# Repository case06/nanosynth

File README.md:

# nanosynth

[![In cooperation with Open Source Ecology Germany](
    https://custom-icon-badges.demolab.com/badge/-OSEG-555555.svg?logo=oseg_logo)](
    https://opensourceecology.de)

Simple synth with MIDI interface, based on Arduino Nano

The KiCAD-sourcefiles of the current version can be viewed or modified with KiCAD version 5.0.2 or higher.

<p></p>

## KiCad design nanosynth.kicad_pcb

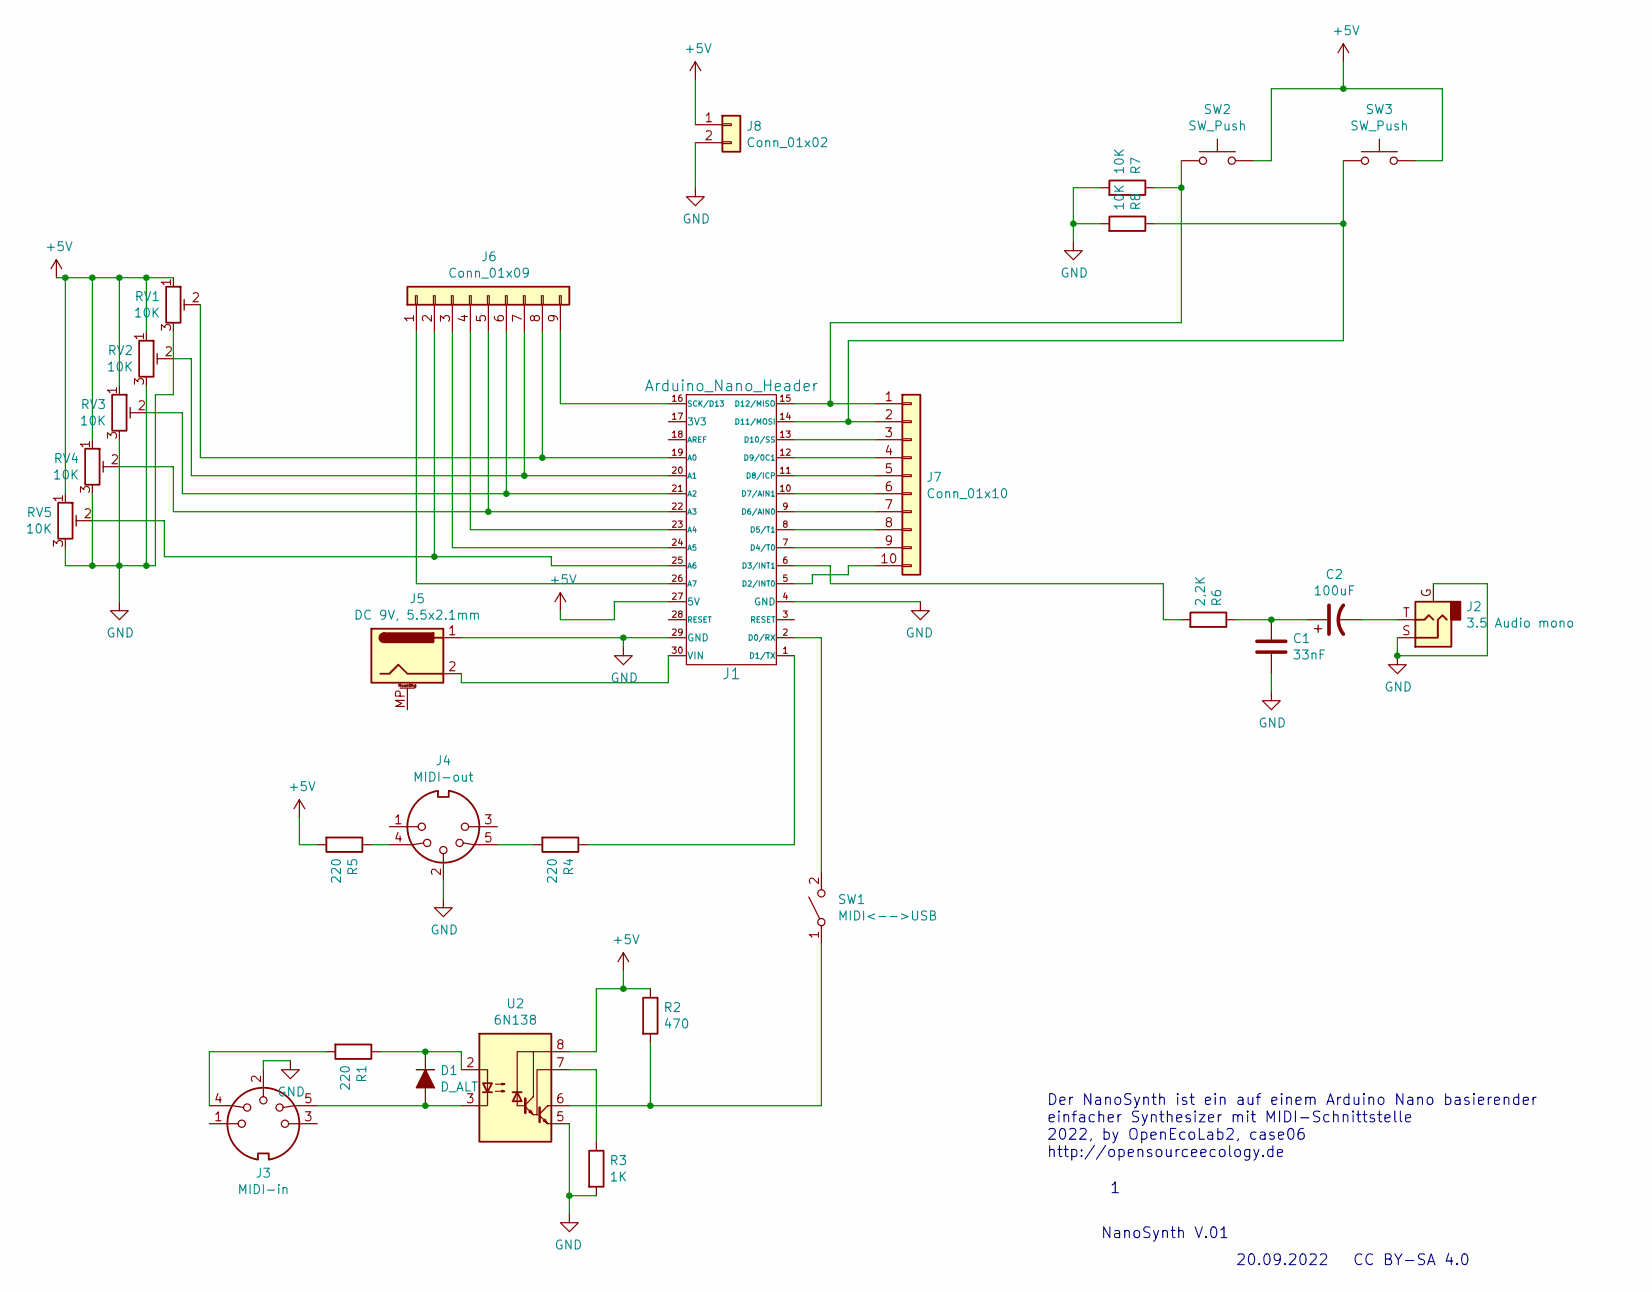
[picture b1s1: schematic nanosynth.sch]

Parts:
C1: 33nF; C_Rect_L7.5mm_W6.5mm_P5.00mm
C2: 100uF; CP_Radial_D8.0mm_P5.00mm
D1: D_ALT; D_DO-35_SOD27_P7.62mm_Horizontal
J1: Arduino_Nano_Header; arduino_nano_header
J2: 3.5 Audio mono; Jack_3.5mm_CUI_SJ1-3533NG_Horizontal
J3: MIDI-in; PinHeader_1x05_P2.54mm_Vertical
J4: MIDI-out; PinHeader_1x05_P2.54mm_Vertical
J5: DC 9V, 5.5x2.1mm; BarrelJack_Horizontal
J6: Conn_01x09; PinHeader_1x09_P2.54mm_Vertical
J7: Conn_01x10; PinHeader_1x10_P2.54mm_Vertical
J8: Conn_01x02; PinHeader_1x02_P2.54mm_Vertical
R1, R4, R5: 220; R_Axial_DIN0309_L9.0mm_D3.2mm_P5.08mm_Vertical
R2: 470; R_Axial_DIN0309_L9.0mm_D3.2mm_P5.08mm_Vertical
R3: 1K; R_Axial_DIN0309_L9.0mm_D3.2mm_P5.08mm_Vertical
R6: 2,2K; R_Axial_DIN0309_L9.0mm_D3.2mm_P5.08mm_Vertical
R7, R8: 10K; R_Axial_DIN0309_L9.0mm_D3.2mm_P5.08mm_Vertical
RV1, RV2, RV3, RV4, RV5: 10K; Potentiometer_Vishay_T73XW_Horizontal
SW1: MIDI<-->USB; PinHeader_1x02_P2.54mm_Vertical
SW2, SW3: SW_Push; PinHeader_1x02_P2.54mm_Vertical
U2: 6N138; DIP-8_W7.62mm_LongPads

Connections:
+5V: J1.27 (5V), J8.1, R2.1, R5.2, RV1.1, RV2.1, RV3.1, RV4.1, RV5.1, SW2.2, SW3.2, U2.8 (VCC)
GND: C1.2, J1.4 (GND), J1.29 (GND), J2.G, J2.S, J3.2, J4.2, J5.1, J8.2, R3.2, R7.2, R8.2, RV1.3, RV2.3, RV3.3, RV4.3, RV5.3, U2.5 (GND)
unnamed: C1.1, C2.1, R6.1
unnamed: C2.2, J2.T
unnamed: D1.1 (K), R1.1, U2.2 (C1)
unnamed: D1.2 (A), J3.5, U2.3 (C2)
unnamed: J1.1 (D1/TX), R4.1
unnamed: J1.2 (D0/RX), SW1.2 (B)
unnamed: J1.5 (D2/INT0), J7.10
unnamed: J1.6 (D3/INT1), R6.2
unnamed: J1.7 (D4/T0), J7.9
unnamed: J1.8 (D5/T1), J7.8
unnamed: J1.9 (D6/AIN0), J7.7
unnamed: J1.10 (D7/AIN1), J7.6
unnamed: J1.11 (D8/ICP), J7.5
unnamed: J1.12 (D9/0C1), J7.4
unnamed: J1.13 (D10/SS), J7.3
unnamed: J1.14 (D11/MOSI), J7.2, R8.1, SW3.1
unnamed: J1.15 (D12/MISO), J7.1, R7.1, SW2.1
unnamed: J1.16 (SCK/D13), J6.9
unnamed: J1.19 (A0), J6.8, RV1.2
unnamed: J1.20 (A1), J6.7, RV2.2
unnamed: J1.21 (A2), J6.6, RV3.2
unnamed: J1.22 (A3), J6.5, RV4.2
unnamed: J1.23 (A4), J6.4
unnamed: J1.24 (A5), J6.3
unnamed: J1.25 (A6), J6.2, RV5.2
unnamed: J1.26 (A7), J6.1
unnamed: J1.30 (VIN), J5.2
unnamed: J3.4, R1.2
unnamed: J4.4, R5.1
unnamed: J4.5, R4.2
unnamed: R2.2, SW1.1 (A), U2.6 (VO2)
unnamed: R3.1, U2.7 (VO1)

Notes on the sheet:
NanoSynth V.01
20.09.2022
Der NanoSynth ist ein auf einem Arduino Nano basierender einfacher Synthesizer mit MIDI-Schnittstelle 2022, by OpenEcoLab2, case06 http://opensourceecology.de
CC BY-SA 4.0

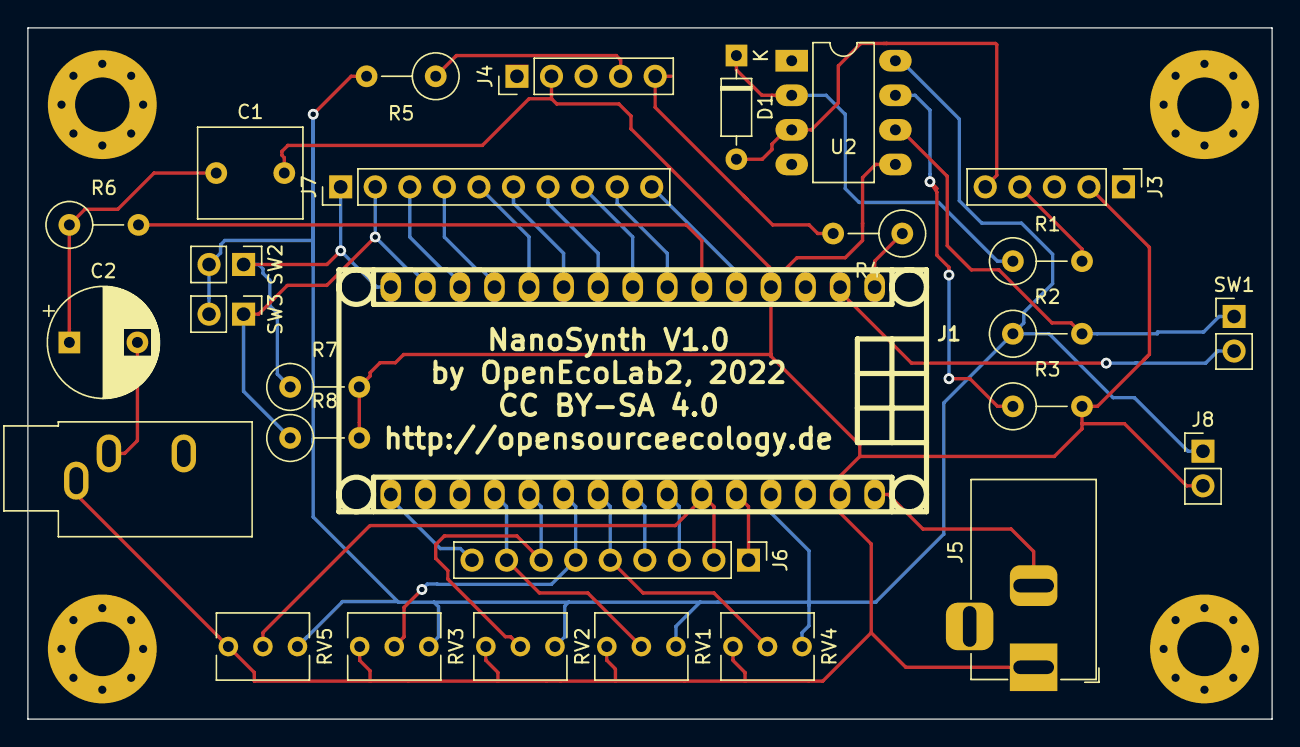
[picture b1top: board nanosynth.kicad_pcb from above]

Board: 2 copper layers, 91.4 x 50.8 mm, 28 parts (0 on the bottom side), 34 nets.

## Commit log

2022-12-01 added oseg custombadge
